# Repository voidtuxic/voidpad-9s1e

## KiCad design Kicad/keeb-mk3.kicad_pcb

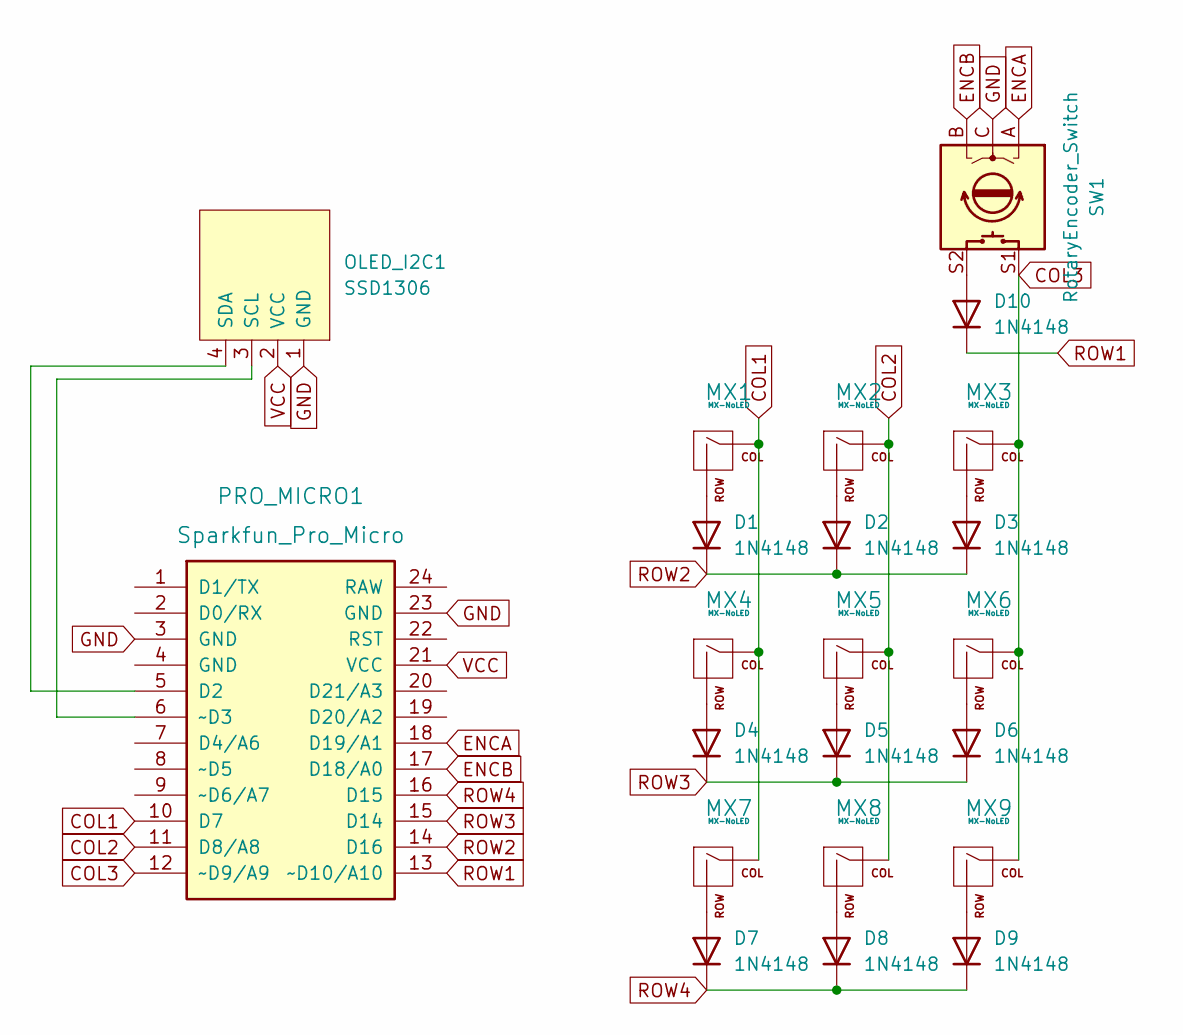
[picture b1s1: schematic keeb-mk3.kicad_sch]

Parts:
D1, D2, D3, D4, D5, D6, D7, D8, D9, D10: 1N4148; D_DO-35_SOD27_P7.62mm_Horizontal
MX1, MX2, MX3, MX4, MX5, MX6, MX7, MX8, MX9: MX-NoLED; SW_Cherry_MX_1.00u_PCB
OLED_I2C1: SSD1306; 128x64OLED
PRO_MICRO1: Sparkfun_Pro_Micro
SW1: RotaryEncoder_Switch; RotaryEncoder_Alps_EC11E-Switch_Vertical_H20mm

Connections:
COL1: MX1.1 (COL), MX4.1 (COL), MX7.1 (COL), PRO_MICRO1.10 (D7)
COL2: MX2.1 (COL), MX5.1 (COL), MX8.1 (COL), PRO_MICRO1.11 (D8/A8)
COL3: MX3.1 (COL), MX6.1 (COL), MX9.1 (COL), PRO_MICRO1.12 (~D9/A9), SW1.S1
ENCA: PRO_MICRO1.18 (D19/A1), SW1.A
ENCB: PRO_MICRO1.17 (D18/A0), SW1.B
GND: OLED_I2C1.1 (GND), PRO_MICRO1.3 (GND), PRO_MICRO1.23 (GND), SW1.C
unnamed: D1.2 (A), MX1.2 (ROW)
unnamed: D2.2 (A), MX2.2 (ROW)
unnamed: D3.2 (A), MX3.2 (ROW)
unnamed: D4.2 (A), MX4.2 (ROW)
unnamed: D5.2 (A), MX5.2 (ROW)
unnamed: D6.2 (A), MX6.2 (ROW)
unnamed: D7.2 (A), MX7.2 (ROW)
unnamed: D8.2 (A), MX8.2 (ROW)
unnamed: D9.2 (A), MX9.2 (ROW)
unnamed: D10.2 (A), SW1.S2
unnamed: OLED_I2C1.3 (SCL), PRO_MICRO1.6 (~D3)
unnamed: OLED_I2C1.4 (SDA), PRO_MICRO1.5 (D2)
ROW1: D10.1 (K), PRO_MICRO1.13 (~D10/A10)
ROW2: D1.1 (K), D2.1 (K), D3.1 (K), PRO_MICRO1.14 (D16)
ROW3: D4.1 (K), D5.1 (K), D6.1 (K), PRO_MICRO1.15 (D14)
ROW4: D7.1 (K), D8.1 (K), D9.1 (K), PRO_MICRO1.16 (D15)
VCC: OLED_I2C1.2 (VCC), PRO_MICRO1.21 (VCC)

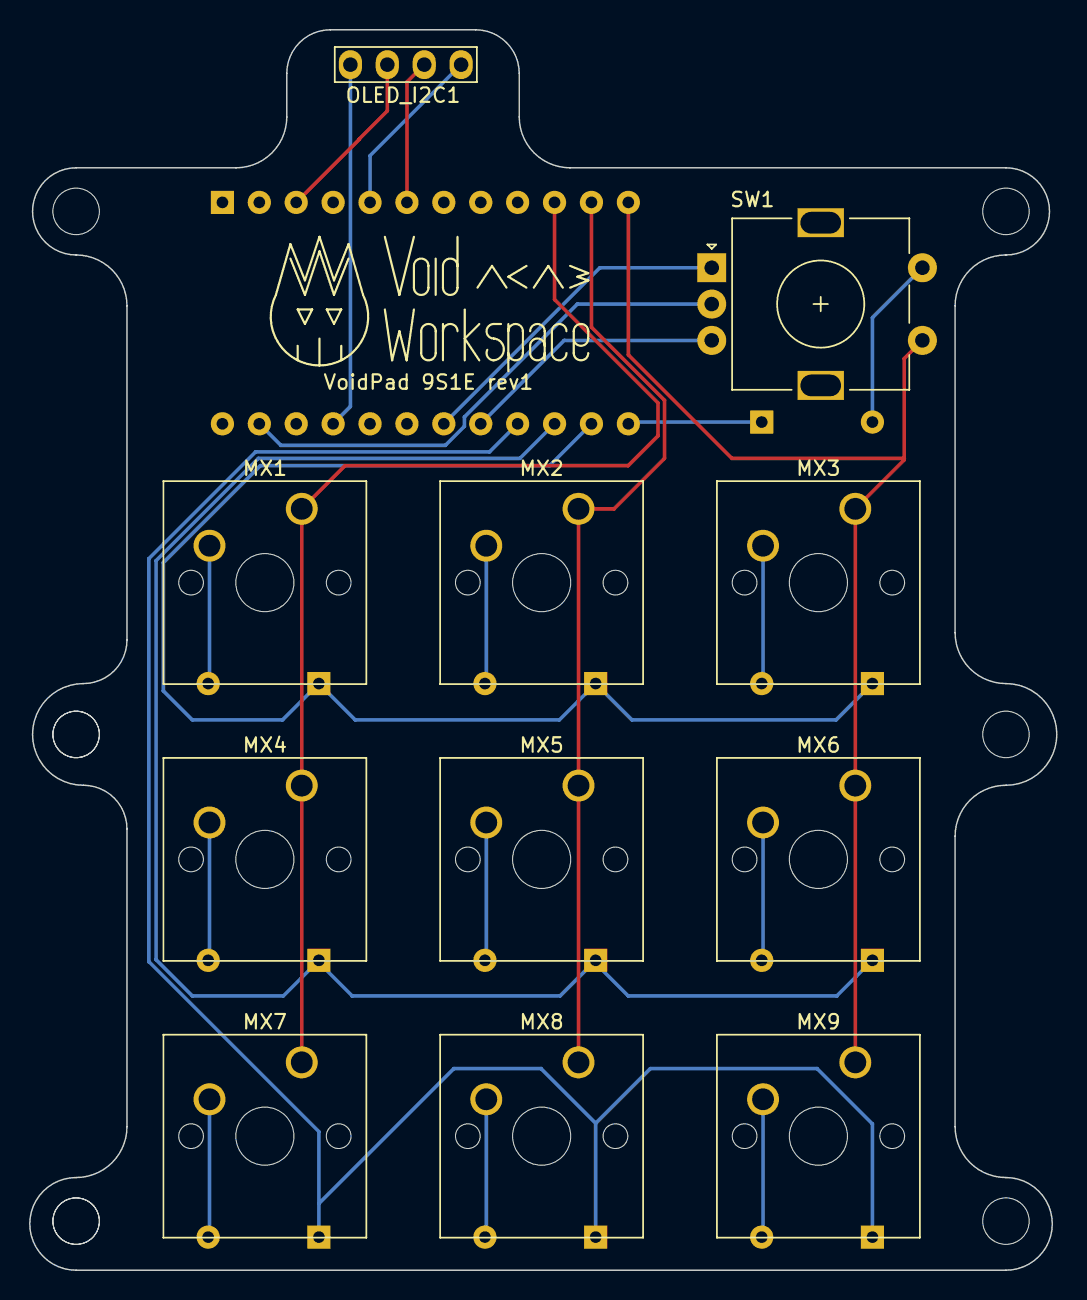
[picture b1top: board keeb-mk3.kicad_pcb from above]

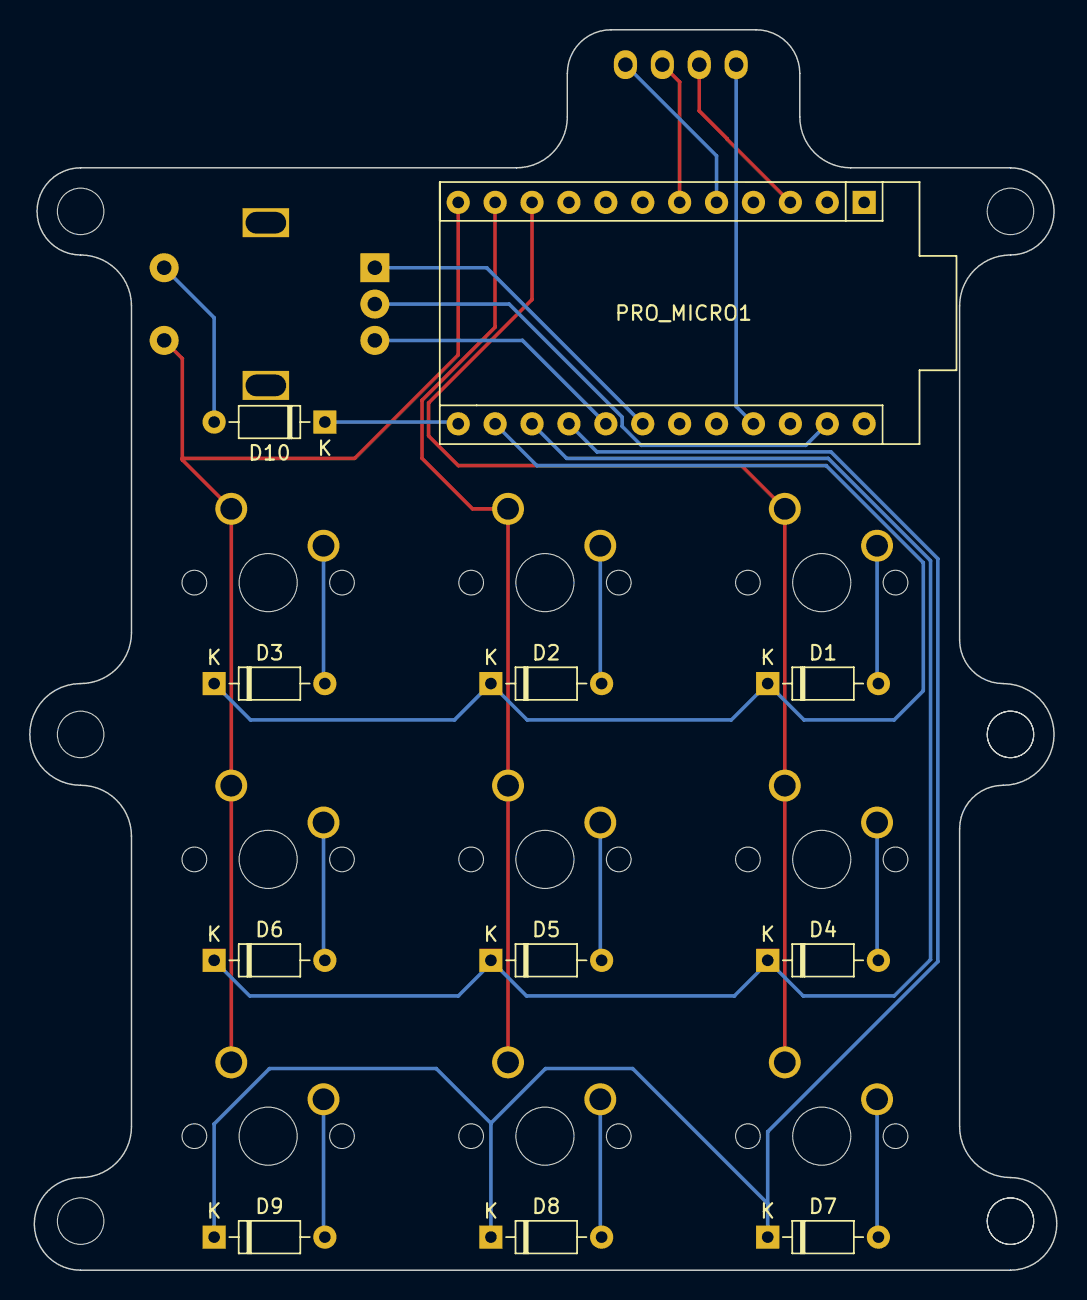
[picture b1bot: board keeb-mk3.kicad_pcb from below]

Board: 2 copper layers, 70.7 x 85.4 mm, 22 parts (11 on the bottom side), 23 nets.

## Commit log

2022-06-01 Create LICENSE
